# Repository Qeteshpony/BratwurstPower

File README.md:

# BratwurstPower

[Hardware Documentation](https://qeteshpony.github.io/BratwurstPower)

### What's this?

A power supply for a complete, Raspberry Pi based ADS-B Receiver Setup with independent power rails for the different components.

We sometimes face the problem that a normal Raspberry Pi power supply does not deliver enough power for the Raspi itself, the SDR Stick and possible other components like a display or even an SSD. 

This board can be mounted underneath a Raspberry Pi and deliver stable 5.x V with up to 3 A to it. 

In addition to that it can supply two USB devices and another external device with also 5.x V and 3 A each, provided the input has enough power and the maximum input current does not surpass 5A. 

Each outputs voltage can be calibrated from ~5.06 to ~5.6 V with a trimpot and the two USB outputs are passing USB2 signals from two USB-C connectors that can be hooked up to the Raspberry Pi. If you need USB3, you can use an external Y-cable. 

## What else is on the board?

The onboard circuitry is powered by its own 3.3V LDO regulator which is fed by the power rail for the Raspberry Pi since that one is always running. The LDO can provide a maximum of 200mA to also power small external loads on the GPIO connector. 

There is an INA219 power monitor connected to the main input and each output with a 10mΩ shunt resistor to measure current and voltage. 

The onboard I2C bus is connected to all of the INA219 and a PCA9557

| Device  | I2C-Address |
|:--------|:------------|
| INA219 Raspi | 0x40   |
| INA219 USB1  | 0x41   |
| INA219 USB2  | 0x42   |
| INA219 EXT   | 0x43   |
| INA219 Main  | 0x44   |
| PCA9557      | 0x1F   |

The PCA9557 I/O expander allows to switch off power to the USB-ports and the external power. It also has an LED connected that can be used for showing a warning state or similar. The other 4 pins are broken out on a header.

| PCA9557 Pin | Function |
|:------------|:---------|
| IO0 | LED  |
| IO1 | GPIO 1 (Opt: Raspi EN) |
| IO2 | GPIO 2 |
| IO3 | GPIO 3 |
| IO4 | GPIO 4 |
| IO5 | USB2 EN |
| IO6 | USB1 EN |
| IO7 | EXT EN |

Each voltage channel has a solder jumper to force-enable it. The USB power rails are also enabled as soon as their input usb port gets connected to the Raspberry Pi. In addition to that, all three external power connections can be controlled by the PCA9557 and there is an optional connection through a solder jumper to even give control over the Raspberry Pi power supply in case the I2C components on this board are controlled externally e.g. by an ESP. 

### External connections and jumpers
| Designator | Function |
|:----------|:---------|
| IN | Main Power supply - can be powered with 7 to 17V DC with a maximum of 5A. Nominal Power: 12V. |
| Raspi | Power supply for the Raspberry Pi. This is the only port that is by default always on. |
| USB1/2 in | USB input for external connections. Connect these to the Raspberry pi with normal USB cables. |
| USB1/2 out | Powered USB output for external components, each with its own power supply. |
| EXT | Power supply for other external components, also independently powered. Needs to be enabled through its solder jumper or by the PCA9557. |
| 2x I2C | I2C connection to either the Raspberry Pi or an external controller. The 3.3V connection is just a path-through between the connectors. |
| OTG | Optional connector to access the Raspberry Pis USB-OTG functionality. |
| GPIO | Optional header to use the free pins of the PCA9557. Keep in mind that the onboard 3.3V LDO can not provide more than 200mA. |
| USB1/2 EN | Solder jumper to force-enable the USB power supplies in case you want to use them without a connection to the Raspberry Pi. |
| EXT EN | Solder jumper to enable the EXT power supply. |
| Raspi EN | Solder jumper to connect the EN pin if the Raspi power supply with IO1 of the PCA9557. This can be used to externally hard-reset the Raspberry Pi and should only be used when the board is controlled by an external controller like an ESP. |
| TP1 | Test point to measure the voltage on the Raspberry Pi power supply. |
| TP2 | Test point to measure the voltage on the USB1 power supply. |
| TP3 | Test point to measure the voltage on the USB2 power supply. |
| TP4 | Test point to measure the voltage on the EXT power supply. |
| RV1 | Calibration Potentiometer for the Raspberry Pi power supply. |
| RV2 | Calibration Potentiometer for the USB1 power supply. |
| RV3 | Calibration Potentiometer for the USB2 power supply. |
| RV4 | Calibration Potentiometer for the EXT power supply. |

### Software

Example software to control and monitor this device with Home Assistant can be found [here](https://github.com/Qeteshpony/BratwurstPower.py).

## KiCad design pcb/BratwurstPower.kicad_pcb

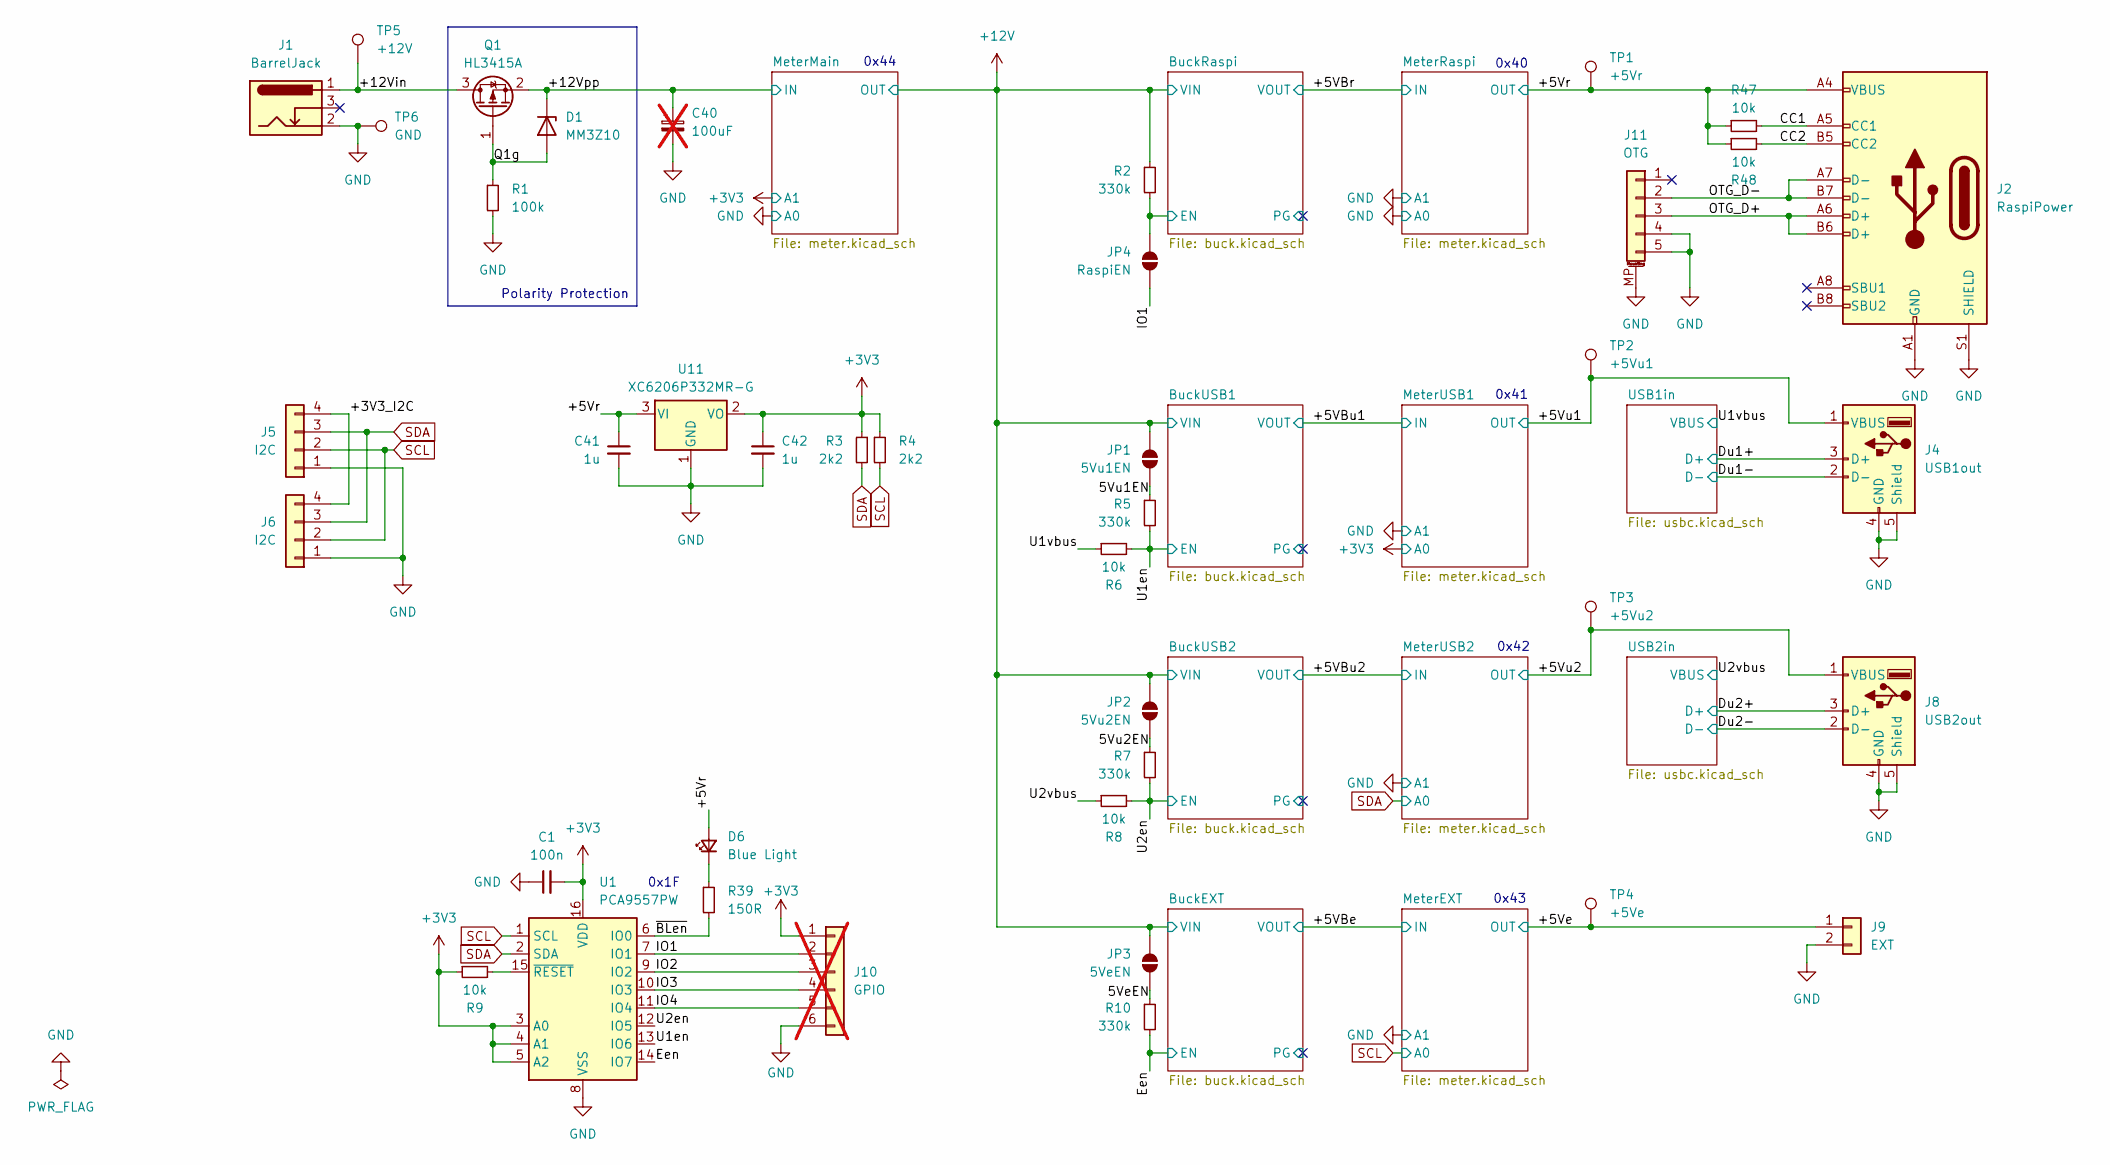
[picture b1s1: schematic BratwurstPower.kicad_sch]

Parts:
C1: 100n; C_0402_1005Metric; LCSC C307331
C40: 100uF; CP_Radial_D6.3mm_P2.50mm; not fitted
C41, C42: 1u; C_0402_1005Metric; LCSC C52923
D1: MM3Z10; D_SOD-323F; LCSC C19077459
D6: Blue Light; LED_0603_1608Metric_Pad1.05x0.95mm_HandSolder; LCSC C72041
J1: BarrelJack; BarrelJack_Combined
J2: RaspiPower; USB_C_Receptacle_GCT_USB4105-xx-A_16P_TopMnt_Horizontal; LCSC C2988369
J4: USB1out; USB_A_Molex_67643_Horizontal; LCSC C2798029
J5, J6: I2C; JST_PH_S4B-PH-K_1x04_P2.00mm_Horizontal; LCSC C265452
J8: USB2out; USB_A_Molex_67643_Horizontal; LCSC C2798029
J9: EXT; JST_XH_S2B-XH-A_1x02_P2.50mm_Horizontal; LCSC C157931
J10: GPIO; PinHeader_1x06_P2.54mm_Vertical; not fitted
J11: OTG; JST_SH_SM05B-SRSS-TB_1x05-1MP_P1.00mm_Horizontal; LCSC C160404
JP1: 5Vu1EN; SolderJumper-2_P1.3mm_Open_TrianglePad1.0x1.5mm
JP2: 5Vu2EN; SolderJumper-2_P1.3mm_Open_TrianglePad1.0x1.5mm
JP3: 5VeEN; SolderJumper-2_P1.3mm_Open_TrianglePad1.0x1.5mm
JP4: RaspiEN; SolderJumper-2_P1.3mm_Open_TrianglePad1.0x1.5mm
Q1: HL3415A; SOT-23; LCSC C28646270
R1: 100k; R_0402_1005Metric; LCSC C25741
R2, R5, R7, R10: 330k; R_0402_1005Metric; LCSC C25778
R3, R4: 2k2; R_0402_1005Metric; LCSC C25879
R6, R8, R9, R47, R48: 10k; R_0402_1005Metric; LCSC C25744
R39: 150R; R_0402_1005Metric; LCSC C25082
TP1: +5Vr; TestPoint_THTPad_D1.0mm_Drill0.5mm
TP2: +5Vu1; TestPoint_THTPad_D1.0mm_Drill0.5mm
TP3: +5Vu2; TestPoint_THTPad_D1.0mm_Drill0.5mm
TP4: +5Ve; TestPoint_THTPad_D1.0mm_Drill0.5mm
TP5: +12V; TestPoint_THTPad_D2.0mm_Drill1.0mm
TP6: GND; TestPoint_THTPad_D2.0mm_Drill1.0mm
U1: PCA9557PW; TSSOP-16_4.4x5mm_P0.65mm; LCSC C141380
U11: XC6206P332MR-G; SOT-23-3; LCSC C5446

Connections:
+3V3: C1.2, C42.1, J10.1, R3.1, R4.1, R9.1, U1.3 (A0), U1.4 (A1), U1.5 (A2), U1.16 (VDD), U11.2 (VO); also elsewhere on the board
+12V: JP1.2 (B), JP2.2 (B), JP3.2 (B), R2.1; also elsewhere on the board
/5VeEN: JP3.1 (A), R10.1
/5Vu1EN: JP1.1 (A), R5.1
/5Vu2EN: JP2.1 (A), R7.1
/+3V3_I2C: J5.4, J6.4
/+5Ve: J9.1, TP4.1; also elsewhere on the board
/+5Vr: C41.1, D6.2 (A), J2.A4 (VBUS), J2.A9 (VBUS), J2.B4 (VBUS), J2.B9 (VBUS), R47.1, R48.1, TP1.1, U11.3 (VI); also elsewhere on the board
/+5Vu1: J4.1 (VBUS), TP2.1; also elsewhere on the board
/+5Vu2: J8.1 (VBUS), TP3.1; also elsewhere on the board
/+12Vin: J1.1, Q1.3 (D), TP5.1
/+12Vpp: C40.1, D1.1 (K), Q1.2 (S); also elsewhere on the board
/BuckRaspi/EN: JP4.2 (B), R2.2; also elsewhere on the board
/CC1: J2.A5 (CC1), R47.2
/CC2: J2.B5 (CC2), R48.2
/Du1+: J4.3 (D+); also elsewhere on the board
/Du1-: J4.2 (D-); also elsewhere on the board
/Du2+: J8.3 (D+); also elsewhere on the board
/Du2-: J8.2 (D-); also elsewhere on the board
/Een: R10.2, U1.14 (IO7); also elsewhere on the board
/IO1: J10.2, JP4.1 (A), U1.7 (IO1)
/IO2: J10.3, U1.9 (IO2)
/IO3: J10.4, U1.10 (IO3)
/IO4: J10.5, U1.11 (IO4)
/OTG_D+: J2.A6 (D+), J2.B6 (D+), J11.3
/OTG_D-: J2.A7 (D-), J2.B7 (D-), J11.2
/Q1g: D1.2 (A), Q1.1 (G), R1.1
/U1en: R5.2, R6.2, U1.13 (IO6); also elsewhere on the board
/U1vbus: R6.1; also elsewhere on the board
/U2en: R7.2, R8.2, U1.12 (IO5); also elsewhere on the board
/U2vbus: R8.1; also elsewhere on the board
/~BLen: R39.2, U1.6 (IO0)
GND: C1.1, C40.2, C41.2, C42.2, J1.2, J2.A1 (GND), J2.A12 (GND), J2.B1 (GND), J2.B12 (GND), J2.S1 (SHIELD), J4.4 (GND), J4.5 (Shield), J5.1, J6.1, J8.4 (GND), J8.5 (Shield), J9.2, J10.6, J11.4, J11.5, J11.MP (MountPin), R1.2, TP6.1, U1.8 (VSS), U11.1 (GND); also elsewhere on the board
unnamed: D6.1 (K), R39.1
unnamed: R9.2, U1.15 (~RESET)
SCL: J5.2, J6.2, R4.2, U1.1 (SCL); also elsewhere on the board
SDA: J5.3, J6.3, R3.2, U1.2 (SDA); also elsewhere on the board

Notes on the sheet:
Polarity Protection
0x41
0x1F
0x44
0x40
0x43
0x42

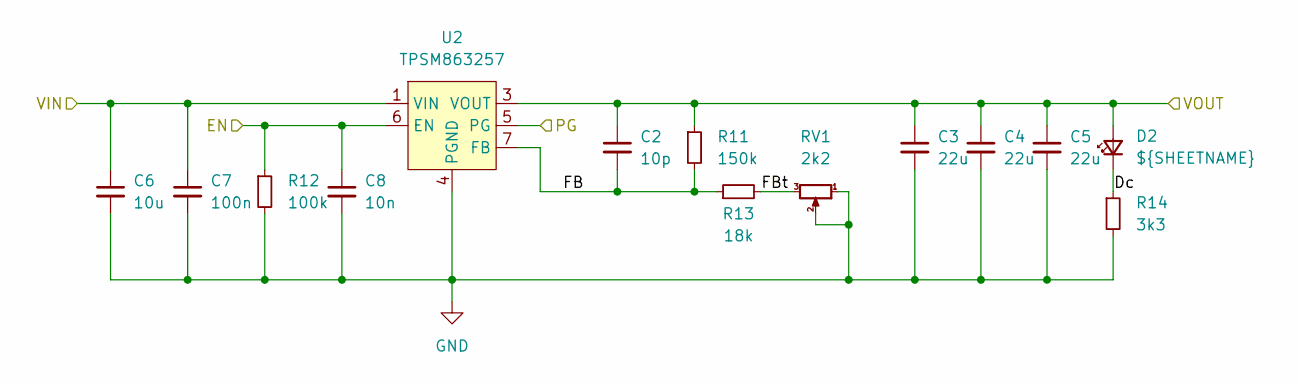
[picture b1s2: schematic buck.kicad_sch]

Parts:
C2: 10p; C_0402_1005Metric; LCSC C32949
C3, C4, C5: 22u; C_0805_2012Metric; LCSC C45783
C6: 10u; C_0805_2012Metric; LCSC C15850
C7: 100n; C_0402_1005Metric; LCSC C307331
C8: 10n; C_0402_1005Metric; LCSC C15195
D2: ${SHEETNAME}; LED_0603_1608Metric; LCSC C72038
R11: 150k; R_0402_1005Metric; LCSC C25755
R12: 100k; R_0402_1005Metric; LCSC C25741
R13: 18k; R_0402_1005Metric; LCSC C25762
R14: 3k3; R_0402_1005Metric; LCSC C25890
RV1: 2k2; Potentiometer_hdk_VG039NCHXT; LCSC C145162
U2: TPSM863257; QFN-FCMOD; LCSC C19190416

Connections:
+12V: C6.1, C7.1, U2.1 (VIN); also elsewhere on the board
/+5VBr: C2.1, C3.1, C4.1, C5.1, D2.2 (A), R11.1, U2.3 (VOUT); also elsewhere on the board
/BuckRaspi/Dc: D2.1 (K), R14.1
/BuckRaspi/EN: C8.1, R12.1, U2.6 (EN); also elsewhere on the board
/BuckRaspi/FB: C2.2, R11.2, R13.1, U2.7 (FB)
/BuckRaspi/FBt: R13.2, RV1.3
/BuckRaspi/PG: U2.5 (PG)
GND: C3.2, C4.2, C5.2, C6.2, C7.2, C8.2, R12.2, R14.2, RV1.1, RV1.2, U2.4 (PGND); also elsewhere on the board

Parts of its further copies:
C9, C16, C23: 10p; C_0402_1005Metric; LCSC C32949
C10, C11, C12, C17, C18, C19, C24, C25, C26: 22u; C_0805_2012Metric; LCSC C45783
C13, C20, C27: 10u; C_0805_2012Metric; LCSC C15850
C14, C21, C28: 100n; C_0402_1005Metric; LCSC C307331
C15, C22, C29: 10n; C_0402_1005Metric; LCSC C15195
R15, R19, R23: 150k; R_0402_1005Metric; LCSC C25755
R16, R20, R24: 100k; R_0402_1005Metric; LCSC C25741
R17, R21, R25: 18k; R_0402_1005Metric; LCSC C25762
R18, R22, R26: 3k3; R_0402_1005Metric; LCSC C25890
RV2, RV3, RV4: 2k2; Potentiometer_hdk_VG039NCHXT; LCSC C145162
U3, U4, U5: TPSM863257; QFN-FCMOD; LCSC C19190416

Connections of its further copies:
+12V: C13.1, C14.1, C20.1, C21.1, C27.1, C28.1, U3.1 (VIN), U4.1 (VIN), U5.1 (VIN); also elsewhere on the board
/+5VBe: C23.1, C24.1, C25.1, C26.1, R23.1, U5.3 (VOUT); also elsewhere on the board
/+5VBu1: C9.1, C10.1, C11.1, C12.1, R15.1, U3.3 (VOUT); also elsewhere on the board
/+5VBu2: C16.1, C17.1, C18.1, C19.1, R19.1, U4.3 (VOUT); also elsewhere on the board
/BuckEXT/Dc: R26.1; also elsewhere on the board
/BuckEXT/FB: C23.2, R23.2, R25.1, U5.7 (FB)
/BuckEXT/FBt: R25.2, RV4.3
/BuckEXT/PG: U5.5 (PG)
/BuckUSB1/Dc: R18.1; also elsewhere on the board
/BuckUSB1/FB: C9.2, R15.2, R17.1, U3.7 (FB)
/BuckUSB1/FBt: R17.2, RV2.3
/BuckUSB1/PG: U3.5 (PG)
/BuckUSB2/Dc: R22.1; also elsewhere on the board
/BuckUSB2/FB: C16.2, R19.2, R21.1, U4.7 (FB)
/BuckUSB2/FBt: R21.2, RV3.3
/BuckUSB2/PG: U4.5 (PG)
/Een: C29.1, R24.1, U5.6 (EN); also elsewhere on the board
/U1en: C15.1, R16.1, U3.6 (EN); also elsewhere on the board
/U2en: C22.1, R20.1, U4.6 (EN); also elsewhere on the board
GND: C10.2, C11.2, C12.2, C13.2, C14.2, C15.2, C17.2, C18.2, C19.2, C20.2, C21.2, C22.2, C24.2, C25.2, C26.2, C27.2, C28.2, C29.2, R16.2, R18.2, R20.2, R22.2, R24.2, R26.2, RV2.1, RV2.2, RV3.1, RV3.2, RV4.1, RV4.2, U3.4 (PGND), U4.4 (PGND), U5.4 (PGND); also elsewhere on the board

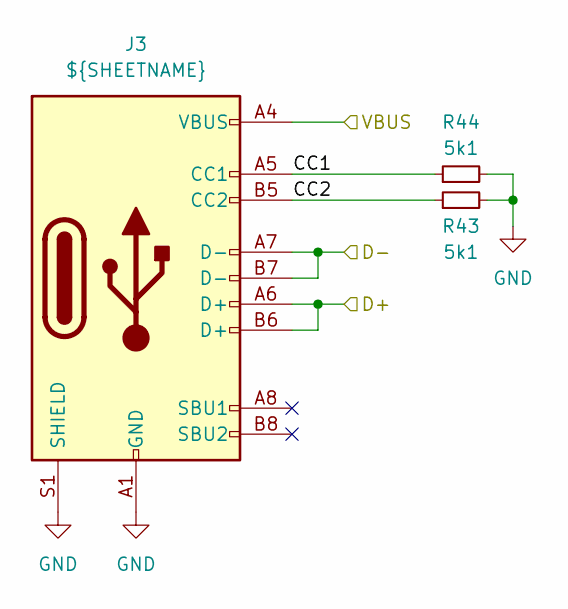
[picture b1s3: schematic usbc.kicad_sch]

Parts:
J3: ${SHEETNAME}; USB_C_Receptacle_GCT_USB4105-xx-A_16P_TopMnt_Horizontal; LCSC C2988369
R43, R44: 5k1; R_0402_1005Metric; LCSC C25905

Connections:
/Du1+: J3.A6 (D+), J3.B6 (D+); also elsewhere on the board
/Du1-: J3.A7 (D-), J3.B7 (D-); also elsewhere on the board
/U1vbus: J3.A4 (VBUS), J3.A9 (VBUS), J3.B4 (VBUS), J3.B9 (VBUS); also elsewhere on the board
/USB1in/CC1: J3.A5 (CC1), R44.1
/USB1in/CC2: J3.B5 (CC2), R43.1
GND: J3.A1 (GND), J3.A12 (GND), J3.B1 (GND), J3.B12 (GND), J3.S1 (SHIELD), R43.2, R44.2; also elsewhere on the board

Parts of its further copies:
R45, R46: 5k1; R_0402_1005Metric; LCSC C25905

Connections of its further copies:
/USB2in/CC1: R45.1; also elsewhere on the board
/USB2in/CC2: R46.1; also elsewhere on the board
GND: R45.2, R46.2; also elsewhere on the board

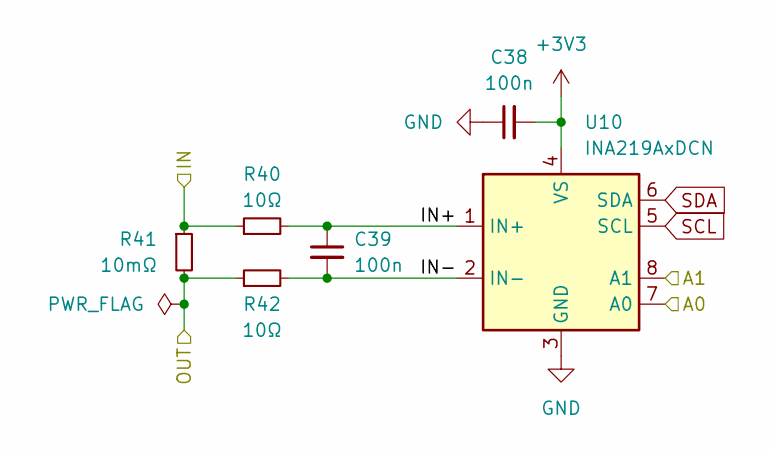
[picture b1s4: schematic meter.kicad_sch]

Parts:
C38, C39: 100n; C_0402_1005Metric; LCSC C307331
R40, R42: 10Ω; R_0402_1005Metric; LCSC C25077
R41: 10mΩ; R_1206_3216Metric; LCSC C2961483
U10: INA219AxDCN; SOT-23-8; LCSC C87469

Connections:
+3V3: C38.2, U10.4 (VS), U10.8 (A1); also elsewhere on the board
+12V: R41.2, R42.1; also elsewhere on the board
/+12Vpp: R40.1, R41.1; also elsewhere on the board
/MeterMain/IN+: C39.1, R40.2, U10.1 (IN+)
/MeterMain/IN-: C39.2, R42.2, U10.2 (IN-)
GND: C38.1, U10.3 (GND), U10.7 (A0); also elsewhere on the board
SCL: U10.5 (SCL); also elsewhere on the board
SDA: U10.6 (SDA); also elsewhere on the board

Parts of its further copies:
C30, C31, C32, C33, C34, C35, C36, C37: 100n; C_0402_1005Metric; LCSC C307331
R27, R29, R30, R32, R33, R35, R36, R38: 10Ω; R_0402_1005Metric; LCSC C25077
R28, R31, R34, R37: 10mΩ; R_1206_3216Metric; LCSC C2961483
U6, U7, U8, U9: INA219AxDCN; SOT-23-8; LCSC C87469

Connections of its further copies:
+3V3: C30.2, C32.2, C34.2, C36.2, U6.4 (VS), U7.4 (VS), U7.7 (A0), U8.4 (VS), U9.4 (VS); also elsewhere on the board
/+5VBe: R36.1, R37.1; also elsewhere on the board
/+5VBr: R27.1, R28.1; also elsewhere on the board
/+5VBu1: R30.1, R31.1; also elsewhere on the board
/+5VBu2: R33.1, R34.1; also elsewhere on the board
/+5Ve: R37.2, R38.1; also elsewhere on the board
/+5Vr: R28.2, R29.1; also elsewhere on the board
/+5Vu1: R31.2, R32.1; also elsewhere on the board
/+5Vu2: R34.2, R35.1; also elsewhere on the board
/MeterEXT/IN+: C37.1, R36.2, U9.1 (IN+)
/MeterEXT/IN-: C37.2, R38.2, U9.2 (IN-)
/MeterRaspi/IN+: C31.1, R27.2, U6.1 (IN+)
/MeterRaspi/IN-: C31.2, R29.2, U6.2 (IN-)
/MeterUSB1/IN+: C33.1, R30.2, U7.1 (IN+)
/MeterUSB1/IN-: C33.2, R32.2, U7.2 (IN-)
/MeterUSB2/IN+: C35.1, R33.2, U8.1 (IN+)
/MeterUSB2/IN-: C35.2, R35.2, U8.2 (IN-)
GND: C30.1, C32.1, C34.1, C36.1, U6.3 (GND), U6.7 (A0), U6.8 (A1), U7.3 (GND), U7.8 (A1), U8.3 (GND), U8.8 (A1), U9.3 (GND), U9.8 (A1); also elsewhere on the board
SCL: U6.5 (SCL), U7.5 (SCL), U8.5 (SCL), U9.5 (SCL), U9.7 (A0); also elsewhere on the board
SDA: U6.6 (SDA), U7.6 (SDA), U8.6 (SDA), U8.7 (A0), U9.6 (SDA); also elsewhere on the board

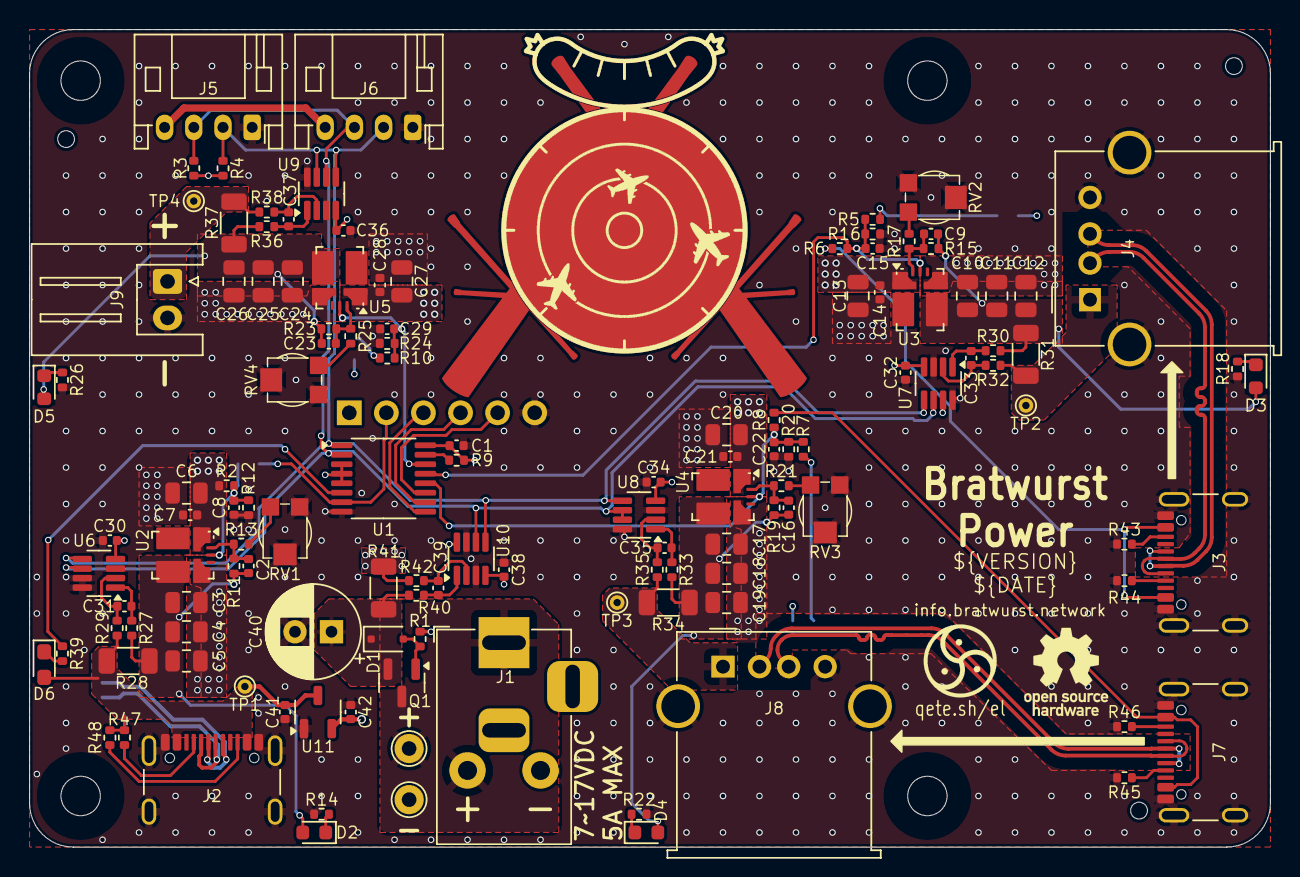
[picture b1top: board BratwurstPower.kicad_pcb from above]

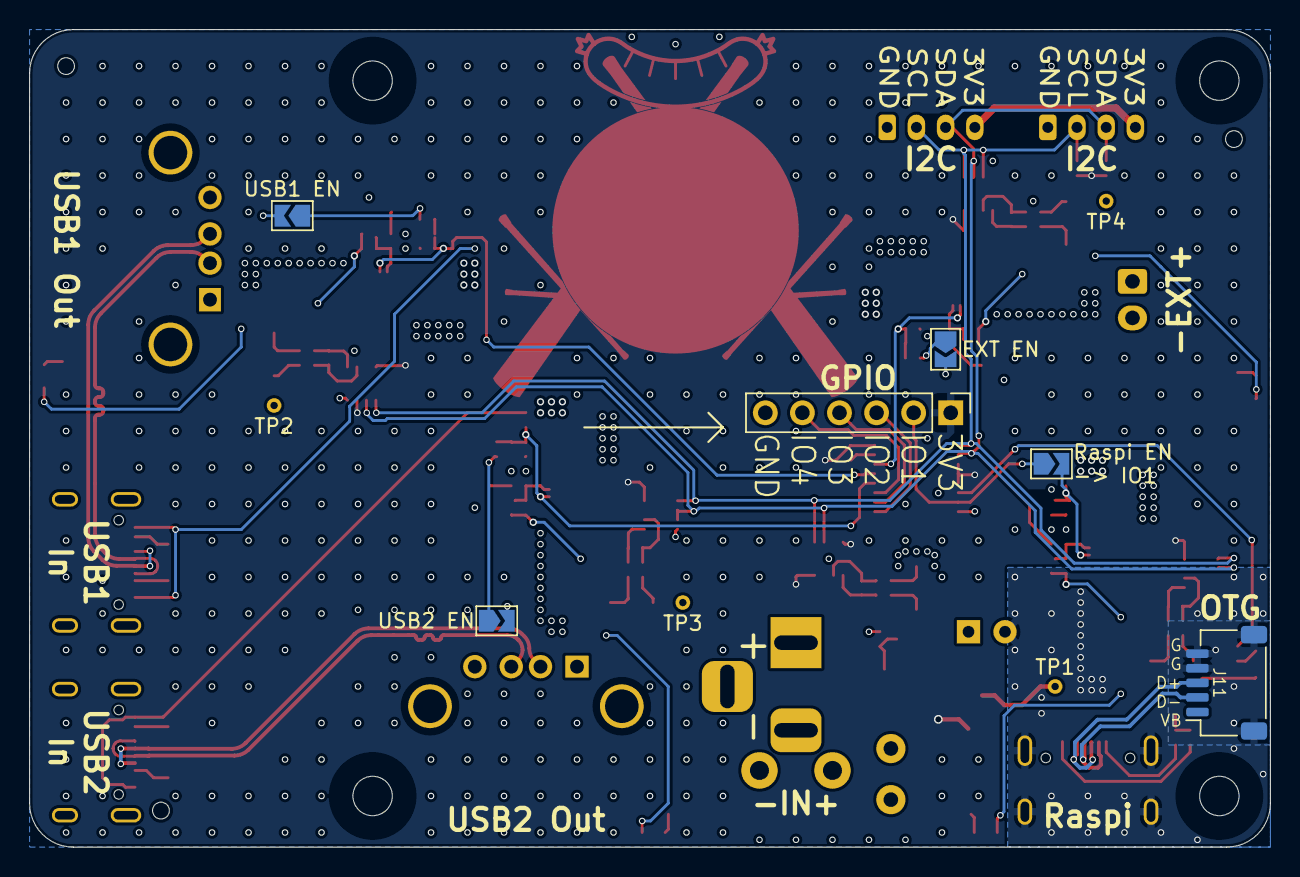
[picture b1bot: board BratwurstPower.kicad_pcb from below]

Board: 4 copper layers, 85.0 x 56.0 mm, 133 parts (6 on the bottom side), 67 nets.

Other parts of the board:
D3: BuckUSB1; LED_0603_1608Metric
D4: BuckUSB2; LED_0603_1608Metric
D5: BuckEXT; LED_0603_1608Metric
J7: USB2in; USB_C_Receptacle_GCT_USB4105-xx-A_16P_TopMnt_Horizontal

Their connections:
/+5VBe: D5.2 (A); also elsewhere on the board
/+5VBu1: D3.2 (A); also elsewhere on the board
/+5VBu2: D4.2 (A); also elsewhere on the board
/BuckEXT/Dc: D5.1 (K); also elsewhere on the board
/BuckUSB1/Dc: D3.1 (K); also elsewhere on the board
/BuckUSB2/Dc: D4.1 (K); also elsewhere on the board
/Du2+: J7.A6 (D+), J7.B6 (D+); also elsewhere on the board
/Du2-: J7.A7 (D-), J7.B7 (D-); also elsewhere on the board
/U2vbus: J7.A4 (VBUS), J7.A9 (VBUS), J7.B4 (VBUS), J7.B9 (VBUS); also elsewhere on the board
/USB2in/CC1: J7.A5 (CC1); also elsewhere on the board
/USB2in/CC2: J7.B5 (CC2); also elsewhere on the board
GND: J7.A1 (GND), J7.A12 (GND), J7.B1 (GND), J7.B12 (GND), J7.S1 (SHIELD); also elsewhere on the board

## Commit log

2024-09-08 feat: initial release
2024-09-08 fix: replace overlapping footprints with custom one
2024-09-10 feat: add more functionality
    - INA power monitor on each output
    - I/O expander to reset usb ports if needed
    - Bratwurst Logo
2024-09-10 docs: update README
2024-09-10 feat: featuritis
    added too much stuff...
2024-09-10 chore: cleanup
2024-09-10 style: add fillets to copper zones
2024-09-10 style: add info tables on bottom silkscreen
2024-09-10 docs: update board properties
2024-09-11 fix: update Bratwurst Logo
2024-09-12 style: update defaults
2024-09-12 feat: add optional input cap
2024-09-12 chore: one shall save before committing
2024-09-12 fix: I2C pull-up strength
2024-09-28 feat: polarity protection for I2C bus
2024-09-28 chore(main): release 1.0.0
2024-09-28 fix: add capacitor to 3V3 rail
2024-09-28 fix: add copper under silkscreen
    to avoid copper planes flooding the bratwurst
2024-09-28 fix: add GND plane on top layer
2024-09-28 fix: via stitching between GND layers
2024-09-28 fix: add clearance around USB traces
2024-09-29 feat!: Replace USB mini and Raspi port with USB-C
    feat: add connector for USB OTG connection
2024-09-29 chore(main): release 2.0.0
2024-09-29 style: replace OTG connector
2024-09-29 docs: add measurements to board
2024-09-30 fix: remove accidental antennas
2024-10-11 ci: add bottom 3d view
2024-10-11 docs: add bottom render
    Also change usb mini to usb c to reflect the actual design
2024-10-13 style: silkscreen cleanup
2024-10-13 fix: part numbers
2024-10-14 feat: add 3.3V LDO for I2C circuitry
2024-10-14 fix: change pots to 2.2kΩ
    fix: part numbers
2024-10-14 fix: add thermal relief to USB ports
2024-10-14 fix: few missing gnd vias
2024-10-14 style: silkscreen typo
2024-10-14 style: silkscreen text
2024-10-15 feat: optional connection RaspiEN to IO1
    In case external control of the I2C bus is taken, this can be used to hard-reset the Raspberry Pi
2024-10-15 chore(main): release 2.1.0
2024-10-15 docs: lots more details
2024-10-15 style: update silkscreen
    Add some more silkscreen information to make identification of components easier
2024-10-26 docs: add link to example software
